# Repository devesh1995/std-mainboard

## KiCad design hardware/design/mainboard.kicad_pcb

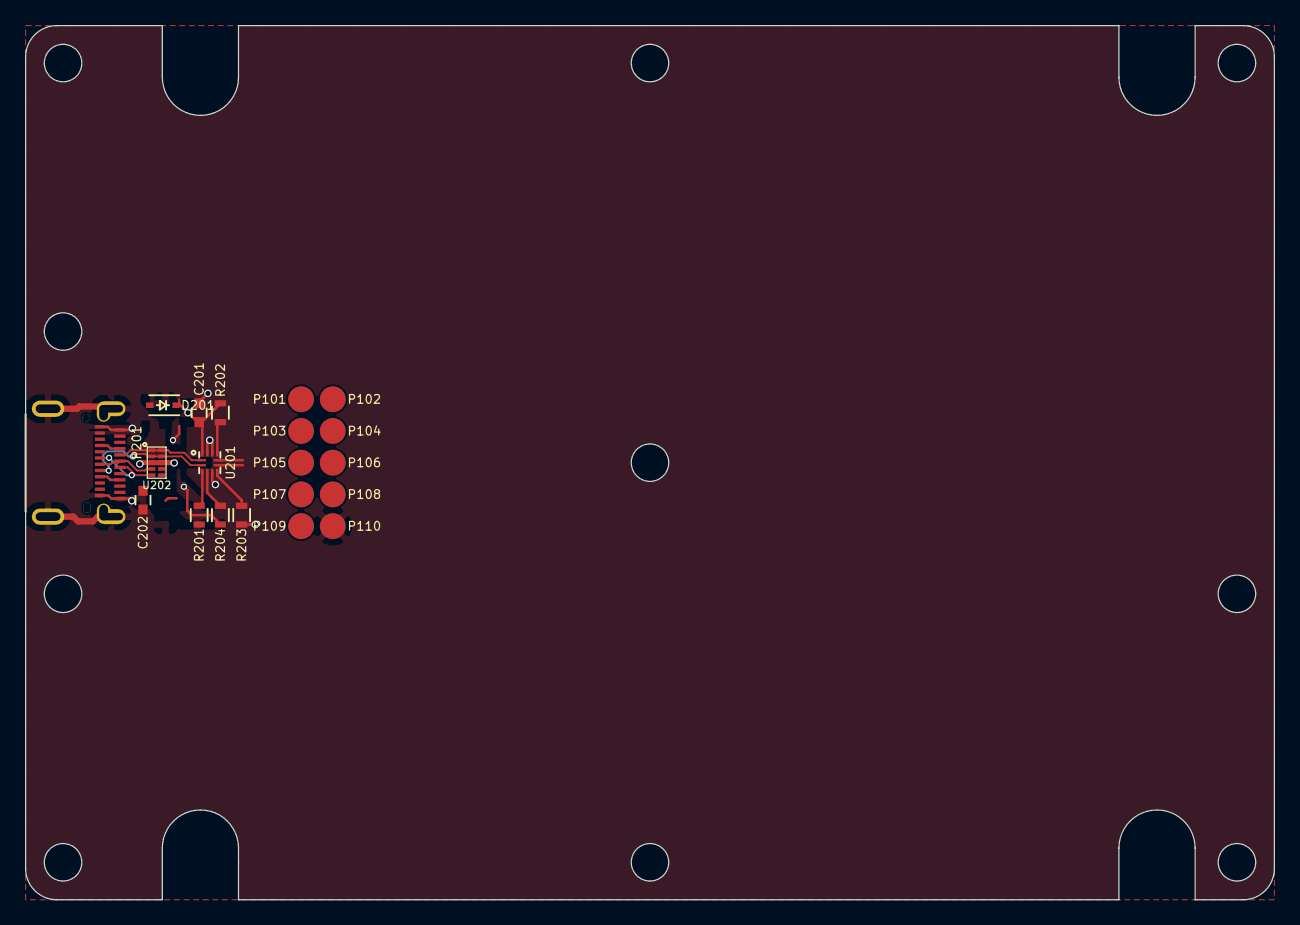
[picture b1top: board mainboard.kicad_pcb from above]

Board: 4 copper layers, 100.0 x 70.0 mm, 20 parts (0 on the bottom side), 11 nets.

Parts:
C201, C202: 100nF; C_0603
D201: Not Installed; SOD-323
P101, P103, P104, P105, P106, P107, P108, P110: GND; 09xx_SPRING_LOADED_POGO_PIN
P102: VDD; 09xx_SPRING_LOADED_POGO_PIN
P109: VBUS; 09xx_SPRING_LOADED_POGO_PIN
P201: USB-C; USB-C-DX07S
R201: 4.7k; R_0603
R202, R203: 200k; R_0603
R204: 900k; R_0603
U201: TUSB320; X2QFN-12
U202: TPD4E05U06; PSON-10_2.5mm_x_1mm

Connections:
3.3v: C201.1, D201.1, R202.1, R203.1, U201.12
/Sheet55D40874/CC1: P201.A5, U201.1, U202.1, U202.10
/Sheet55D40874/CC2: P201.B5, U201.2, U202.2, U202.9
/Sheet55D40874/D+: P201.A6, P201.B6, U202.4, U202.7
/Sheet55D40874/D-: P201.A7, P201.B7, U202.5, U202.6
/Sheet55D40874/INT: R203.2, U201.6
/Sheet55D40874/VBUS: C202.1, D201.2, P201.A4, P201.A9, P201.B4, P201.B9, R204.1
GND: C201.2, C202.2, P110.1, P201.A1, P201.A12, P201.B1, P201.B12, P201.SH, R201.2, U201.5, U201.10, U201.11, U202.3, U202.8
unnamed: R201.1, U201.3
unnamed: R202.2, U201.9
unnamed: R204.2, U201.4

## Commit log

2015-08-19 First automated commit of the project
2015-08-19 Added hardware design files with USB C connector and a draft of the board chassis
